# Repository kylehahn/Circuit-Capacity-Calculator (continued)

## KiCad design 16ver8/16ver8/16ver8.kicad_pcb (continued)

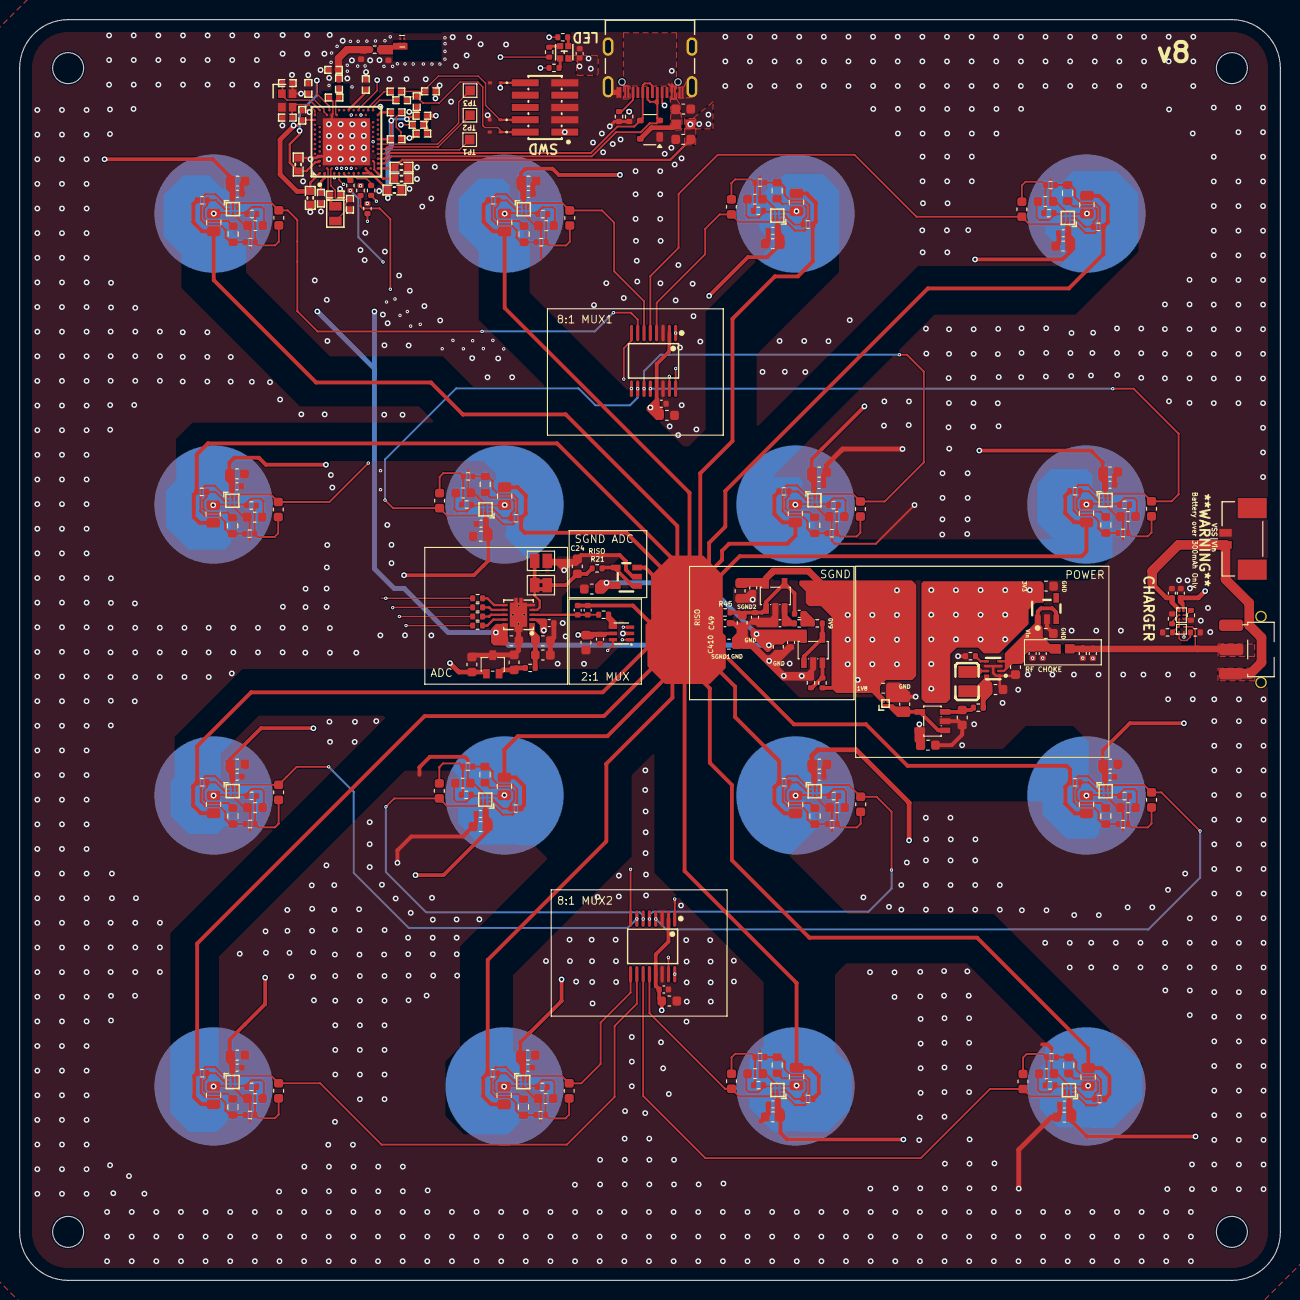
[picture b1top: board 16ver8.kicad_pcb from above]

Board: 4 copper layers, 130.0 x 130.0 mm, 297 parts (0 on the bottom side), 175 nets.

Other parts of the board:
H1, H2, H3, H4: MountingHole; MountingHole_3.2mm_M3

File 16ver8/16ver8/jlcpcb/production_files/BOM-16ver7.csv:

Comment,Designator,Footprint,LCSC,Quantity
0.1u,"C41,C45",C_0402_1005Metric,C1525,2
0.1u,C111,C_0603_1608Metric,C45000,1
0.47u,C24,C_0603_1608Metric,C77052,1
0.5pF,C1212,CAPC1005X04L,C76911,1
0.8pF,C1211,CAPC1005X04L,C76915,1
1,R111,R_0402_1005Metric,C25086,1
1.0µF,"C125,C129",CAPC1608X06L,C29936,2
1.6k,"R8101,R8102,R811,R8111,R8112,R812,R8121,R8122,R8131,R8132,R8141,R8142,R8151,R8152,R8161,R8162,R821,R822,R831,R832,R841,R842,R851,R852,R861,R862,R871,R872,R881,R882,R891,R892",R_0402_1005Metric,C4908,32
1.74k,R31,R_0402_1005Metric,C163482,1
100M,"R7101,R711,R7111,R7121,R7131,R7141,R7151,R7161,R721,R731,R741,R751,R761,R771,R781,R791",R_0805_2012Metric,C169373,16
100n,"C13,C14,C49,C61,C7101,C711,C7111,C7121,C7131,C7141,C7151,C7161,C721,C731,C741,C751,C761,C771,C781,C791,C91,C93,C95",C_0402_1005Metric,C71629,23
100nF,"C1210,C1214,C124,C128",CAPC1005X04L,C71629,4
100pF,C1215,CAPC1005X04L,C26409,1
10k,"R64,R7102,R7112,R712,R7122,R7132,R7142,R7152,R7162,R722,R732,R742,R752,R762,R772,R782,R792",CAPC1005X04L,C25744,17
10u,"C112,C32,C410,C8102,C8112,C812,C8122,C8132,C8142,C8152,C8162,C822,C832,C842,C852,C862,C872,C882,C892",C_0603_1608Metric,C77044,19
12pF,"C121,C1216,C1217,C122",CAPC1005X04L,C161304,4
1M,"R7103,R7113,R7123,R713,R7133,R7143,R7153,R7163,R723,R733,R743,R753,R763,R773,R783,R793",R_0603_1608Metric,C22935,16
1k,R101,R_0402_1005Metric,C11702,1
1n,"C51,C52",C_0603_1608Metric,C1588,2
1n,"C11,C12,C98",C_0402_1005Metric,C76947,3
1u,"C113,C43,C44",C_0402_1005Metric,C15684,3
1u,"C114,C15,C16,C21,C22,C23,C33,C34,C35,C36,C42,C46,C8101,C811,C8111,C8121,C8131,C8141,C8151,C8161,C821,C831,C841,C851,C861,C871,C881,C891",C_0603_1608Metric,C29936,28
2.2Mega,"R41,R42",R_0402_1005Metric,C11490,2
2.2u,"C7102,C7112,C712,C7122,C7132,C7142,C7152,C7162,C722,C732,C742,C752,C762,C772,C782,C792,C92,C94,C96",C_0603_1608Metric,C106213,19
22,"R112,R121,R122,R123,R124,R21,R45,R61,R62,R63,R91",R_0402_1005Metric,C25092,11
249,R103,R_0402_1005Metric,C25096,1
3.16k,"R32,R43,R44",R_0402_1005Metric,C11462,3
32.768kHz,X122,CRYSTAL-SMD_L2.0-W1.2,C5136974,1
33,"R113,R114,R115",R_0402_1005Metric,C25105,3
330,R102,R_0402_1005Metric,C12246,1
4.7nH,L121,INDC1005X04L,C86065,1
4.7u,C31,C_0603_1608Metric,C389010,1
4.7µF,"C123,C126,C127",CAPC1608X06L,C389010,3
47k,"R65,R66",CAPC1005X04L,C25792,2
47n,C97,C_0402_1005Metric,C77012,1
5.1k,"R51,R52",R_0402_1005Metric,C25905,2
533980271,J11,MOLEX_533980271,C122410,1
820pF,C1213,CAPC1005X04L,C237511,1
ADS8867IDRCR,U111,WSON-10_L3.0-W3.0-P0.50-BL-EP,C545498,1
BLM18EG101TN1D,"FL11,FL51",BEADC1608X65N,C76893,2
DFE201612E-2R2M=P2,L1,L0806,C337893,1
ESD9M5.0ST5G,"D61,D62,D63",SODFL1060X40N,C242267,3
FTSH-105-01-F-DV-K,H61,HDR-SMD_FTSH-105-01-F-DV-K,C5382952,1
K3-1280S-L1,SW11,SW_Nidec_CAS-120A1,C223845,1
OPA2392YBJR,"U7101,U711,U7111,U7121,U7131,U7141,U7151,U7161,U721,U731,U741,U751,U761,U771,U781,U791",DSBGA-9_L1.2-W1.2-R3-C3-P0.40-BL,C5946032,16
OPA320AIDBVT,U22,SOT-23-5_L2.9-W1.6-P0.95-LS2.8-BL,C206063,1
OPA333AIDBVR,U41,SOT-23-5_L3.0-W1.7-P0.95-LS2.8-BR,C30878,1
PRTR5V0U2X,D51,SOT-143,C12333,1
REF3330AIDCKR,U21,SC-70-3_L2.0-W1.3-P0.65-LS2.1-BL,C2157700,1
SZYY1615RGB-B 4PIN,D101,LED-SMD_4P-L1.6-W1.5-TR-1,C3029071,1
TLV9001IDBVR,"U32,U42",SOT-23-5_L3.0-W1.7-P0.95-LS2.8-BR,C398363,2
TMUX1108PWR,"U91,U92",TSSOP-16_L5.0-W4.4-P0.65-LS6.4-BL,C1021800,2
TMUX1248DCKR,U93,SC-70-6_L2.0-W1.3-P0.65-LS2.2-BL,C3656915,1
TPS62840DLCR,U31,VSON-8_L2.0-W1.5-P0.50-BL,C2071859,1
TPS7A2018YCKR,U33,BGA-4_L0.6-W0.6-P0.35-R2-C2-TL_TPS7A2012PYCJR,C41613873,1
TPS7A2033YCKR,U11,BGA-4_L0.6-W0.6-P0.35-R2-C2-TL_TPS7A2012PYCJR,C42038768,1
TYPE-C16PIN,J51,CONN16_C16PIN_SHN,C393939,1
X201632MMB4SI,X121,CRYSTAL-SMD_4P-L2.0-W1.6-BL,C383840,1
nRF52840-QIAA,U121,AQFN50P700X700X85_HS-74N,C190794,1
TestPoint,TP2,TestPoint_Pad_1.0x1.0mm,,1
TestPoint,TP1,TestPoint_Pad_1.0x1.0mm,,1
TestPoint,TP3,TestPoint_Pad_1.0x1.0mm,,1
NC,C47,C_0402_1005Metric,,1
NC,C48,C_0603_1608Metric,,1

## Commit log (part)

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2026-05-08 for claude code
2026-05-08 Rename project from sensor3d to circuit_capacity_calculator
2026-05-08 Pin vcpkg builtin-baseline
2026-05-09 Milestone 1: data model + JSON I/O + tests
